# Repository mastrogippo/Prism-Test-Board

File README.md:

# Prism Test Board

[Writeup and pics here]( https://www.mastrogippo.it/2019/09/board-testing-its-fun-they-said/ )

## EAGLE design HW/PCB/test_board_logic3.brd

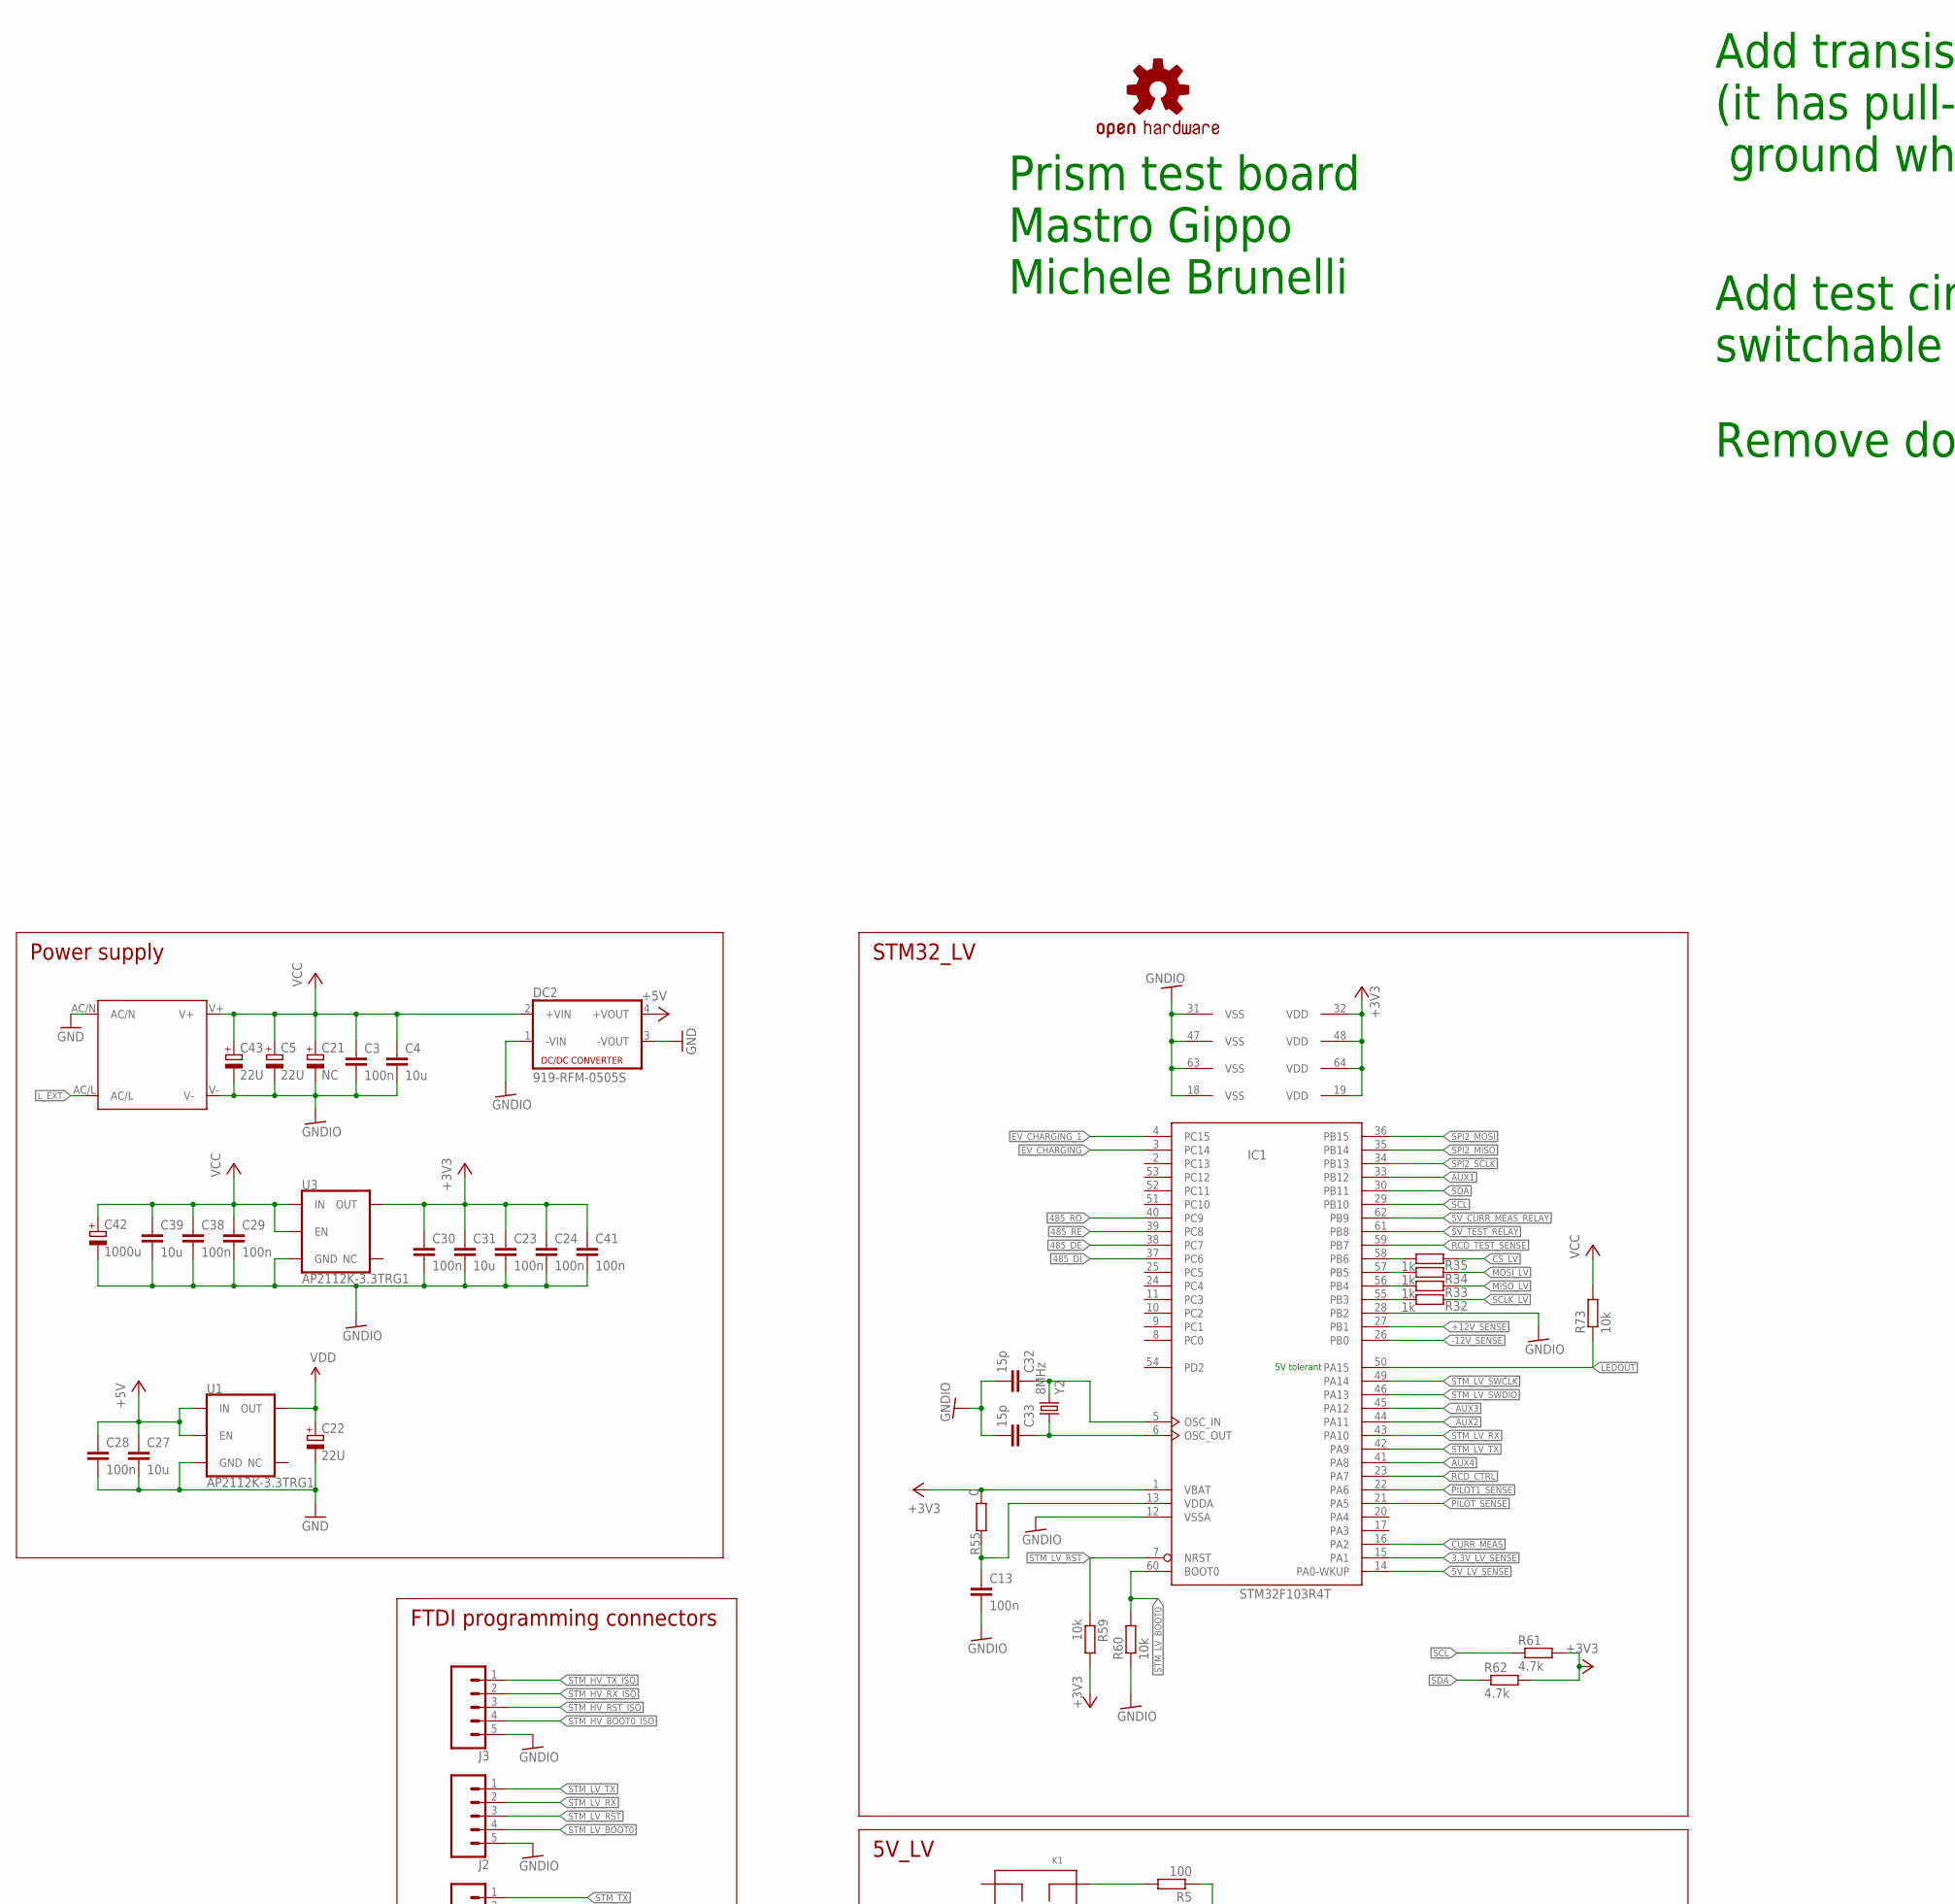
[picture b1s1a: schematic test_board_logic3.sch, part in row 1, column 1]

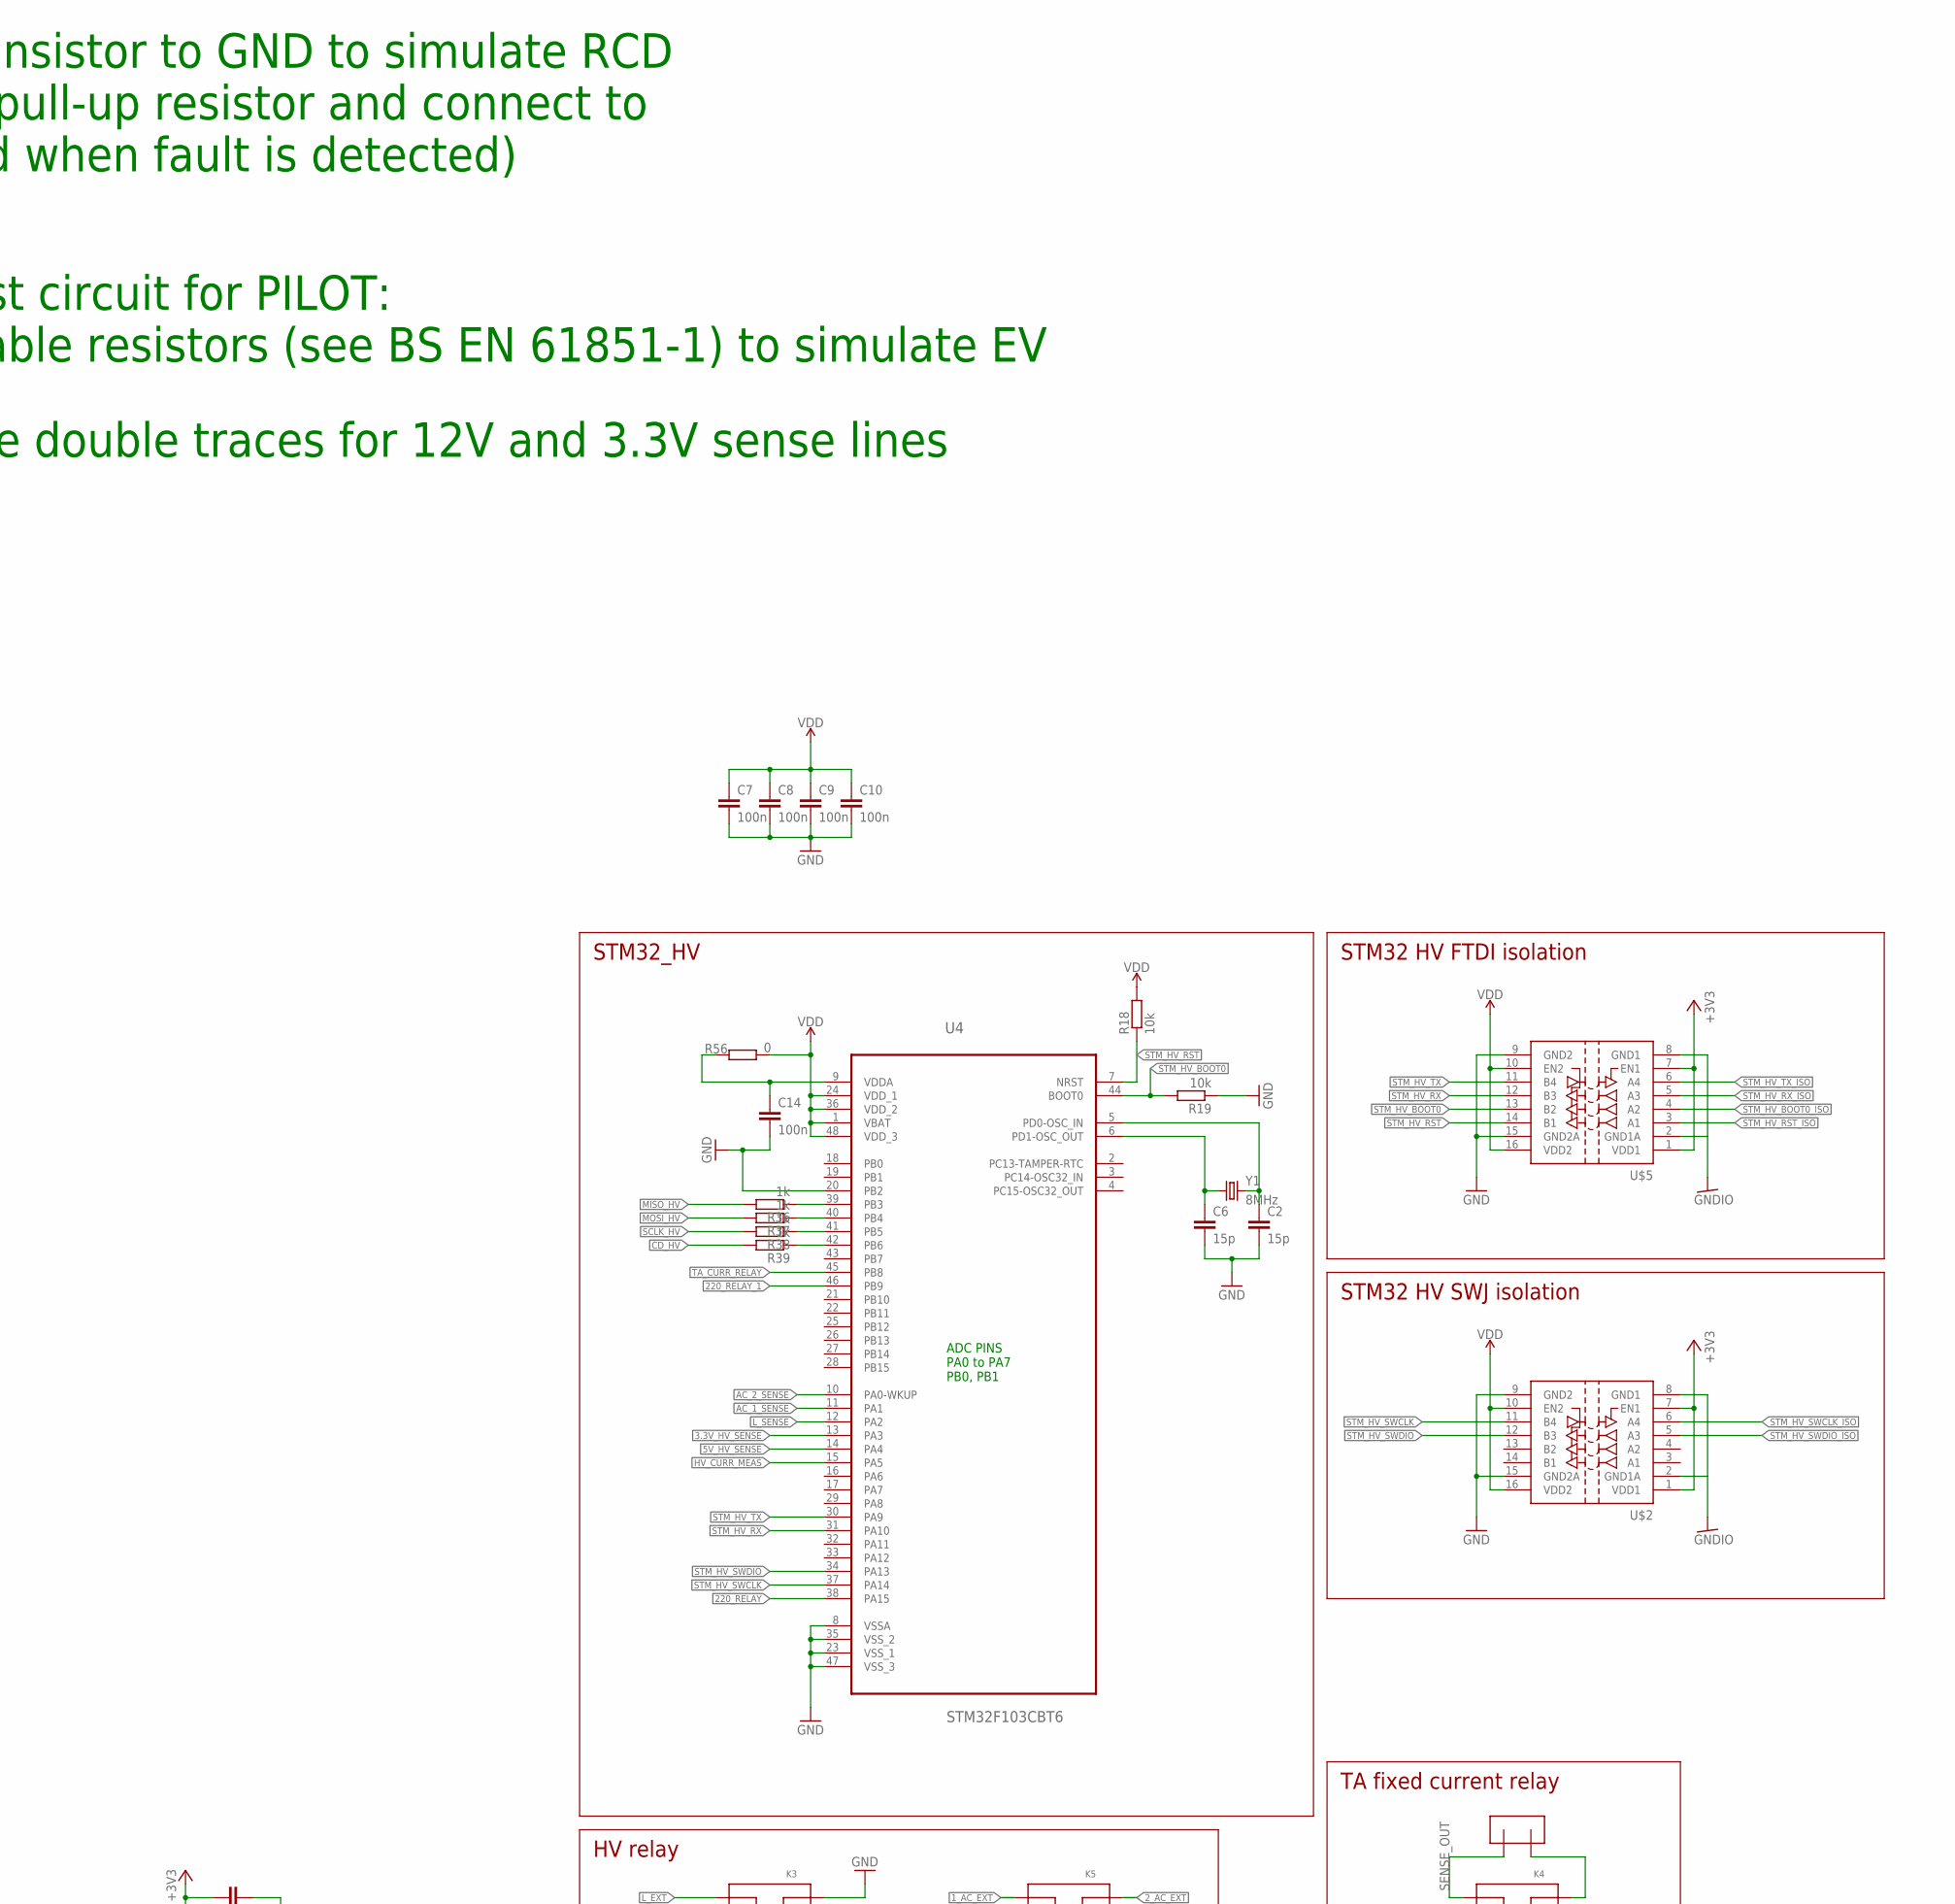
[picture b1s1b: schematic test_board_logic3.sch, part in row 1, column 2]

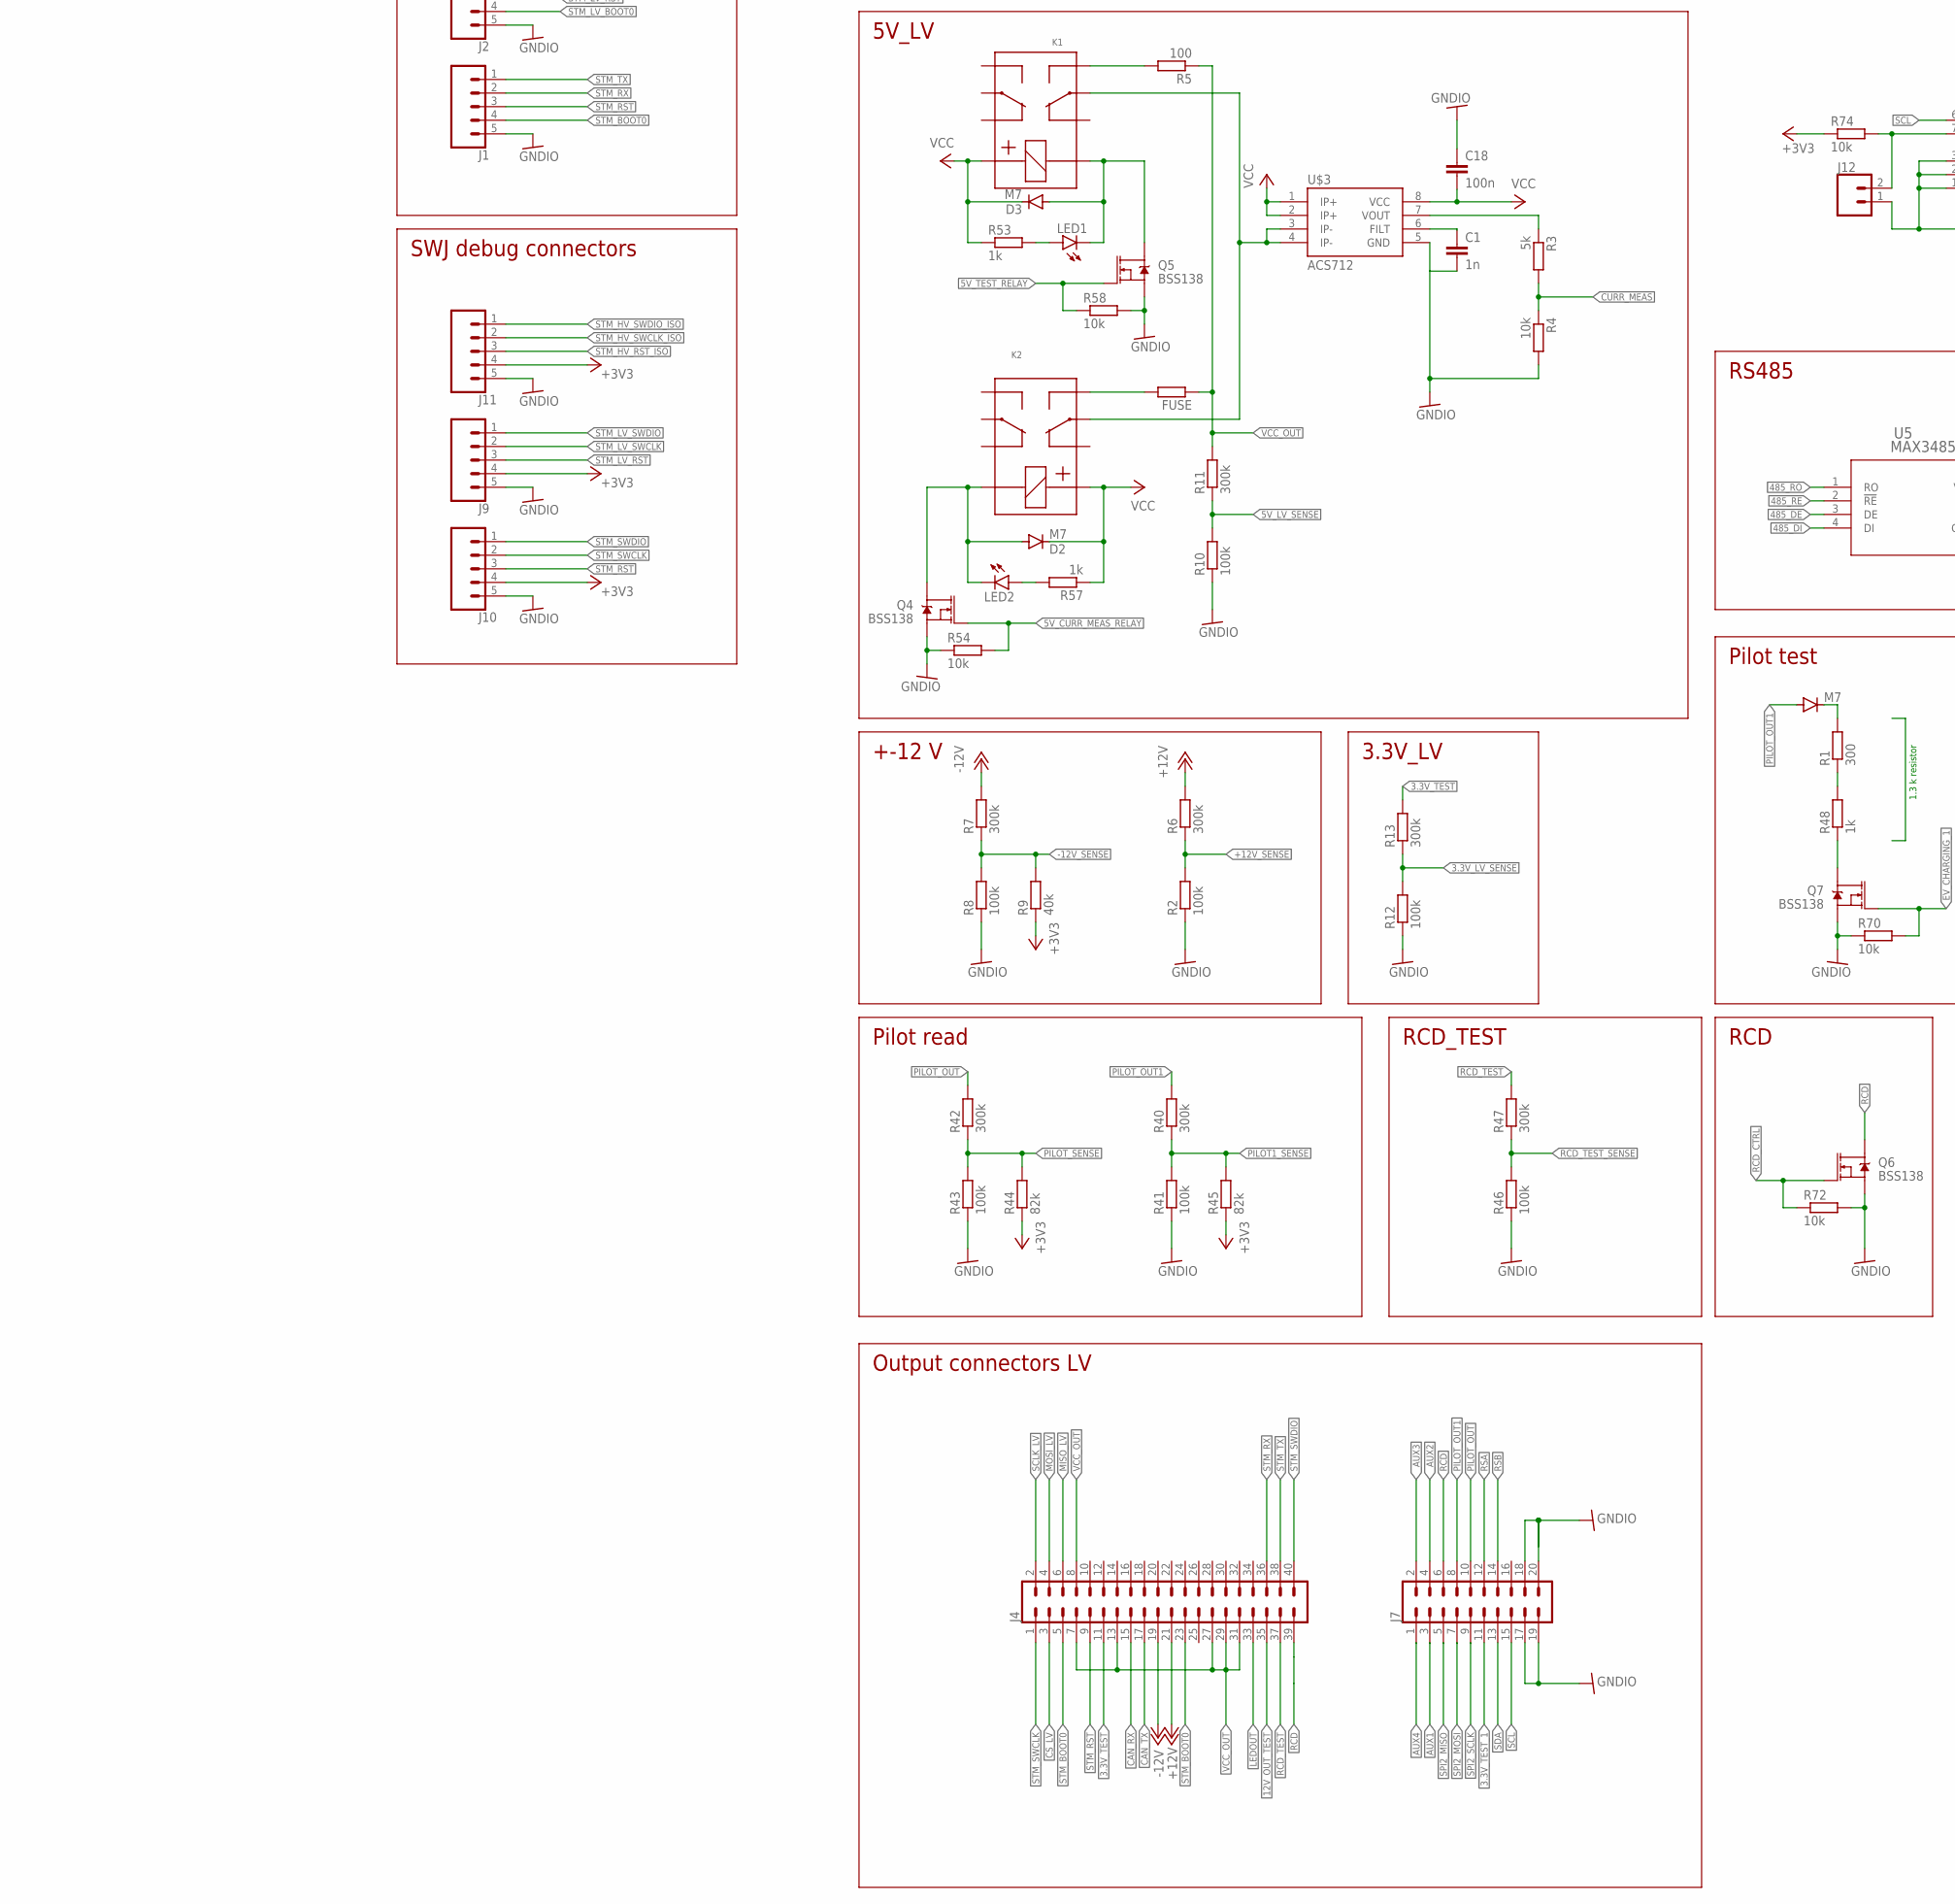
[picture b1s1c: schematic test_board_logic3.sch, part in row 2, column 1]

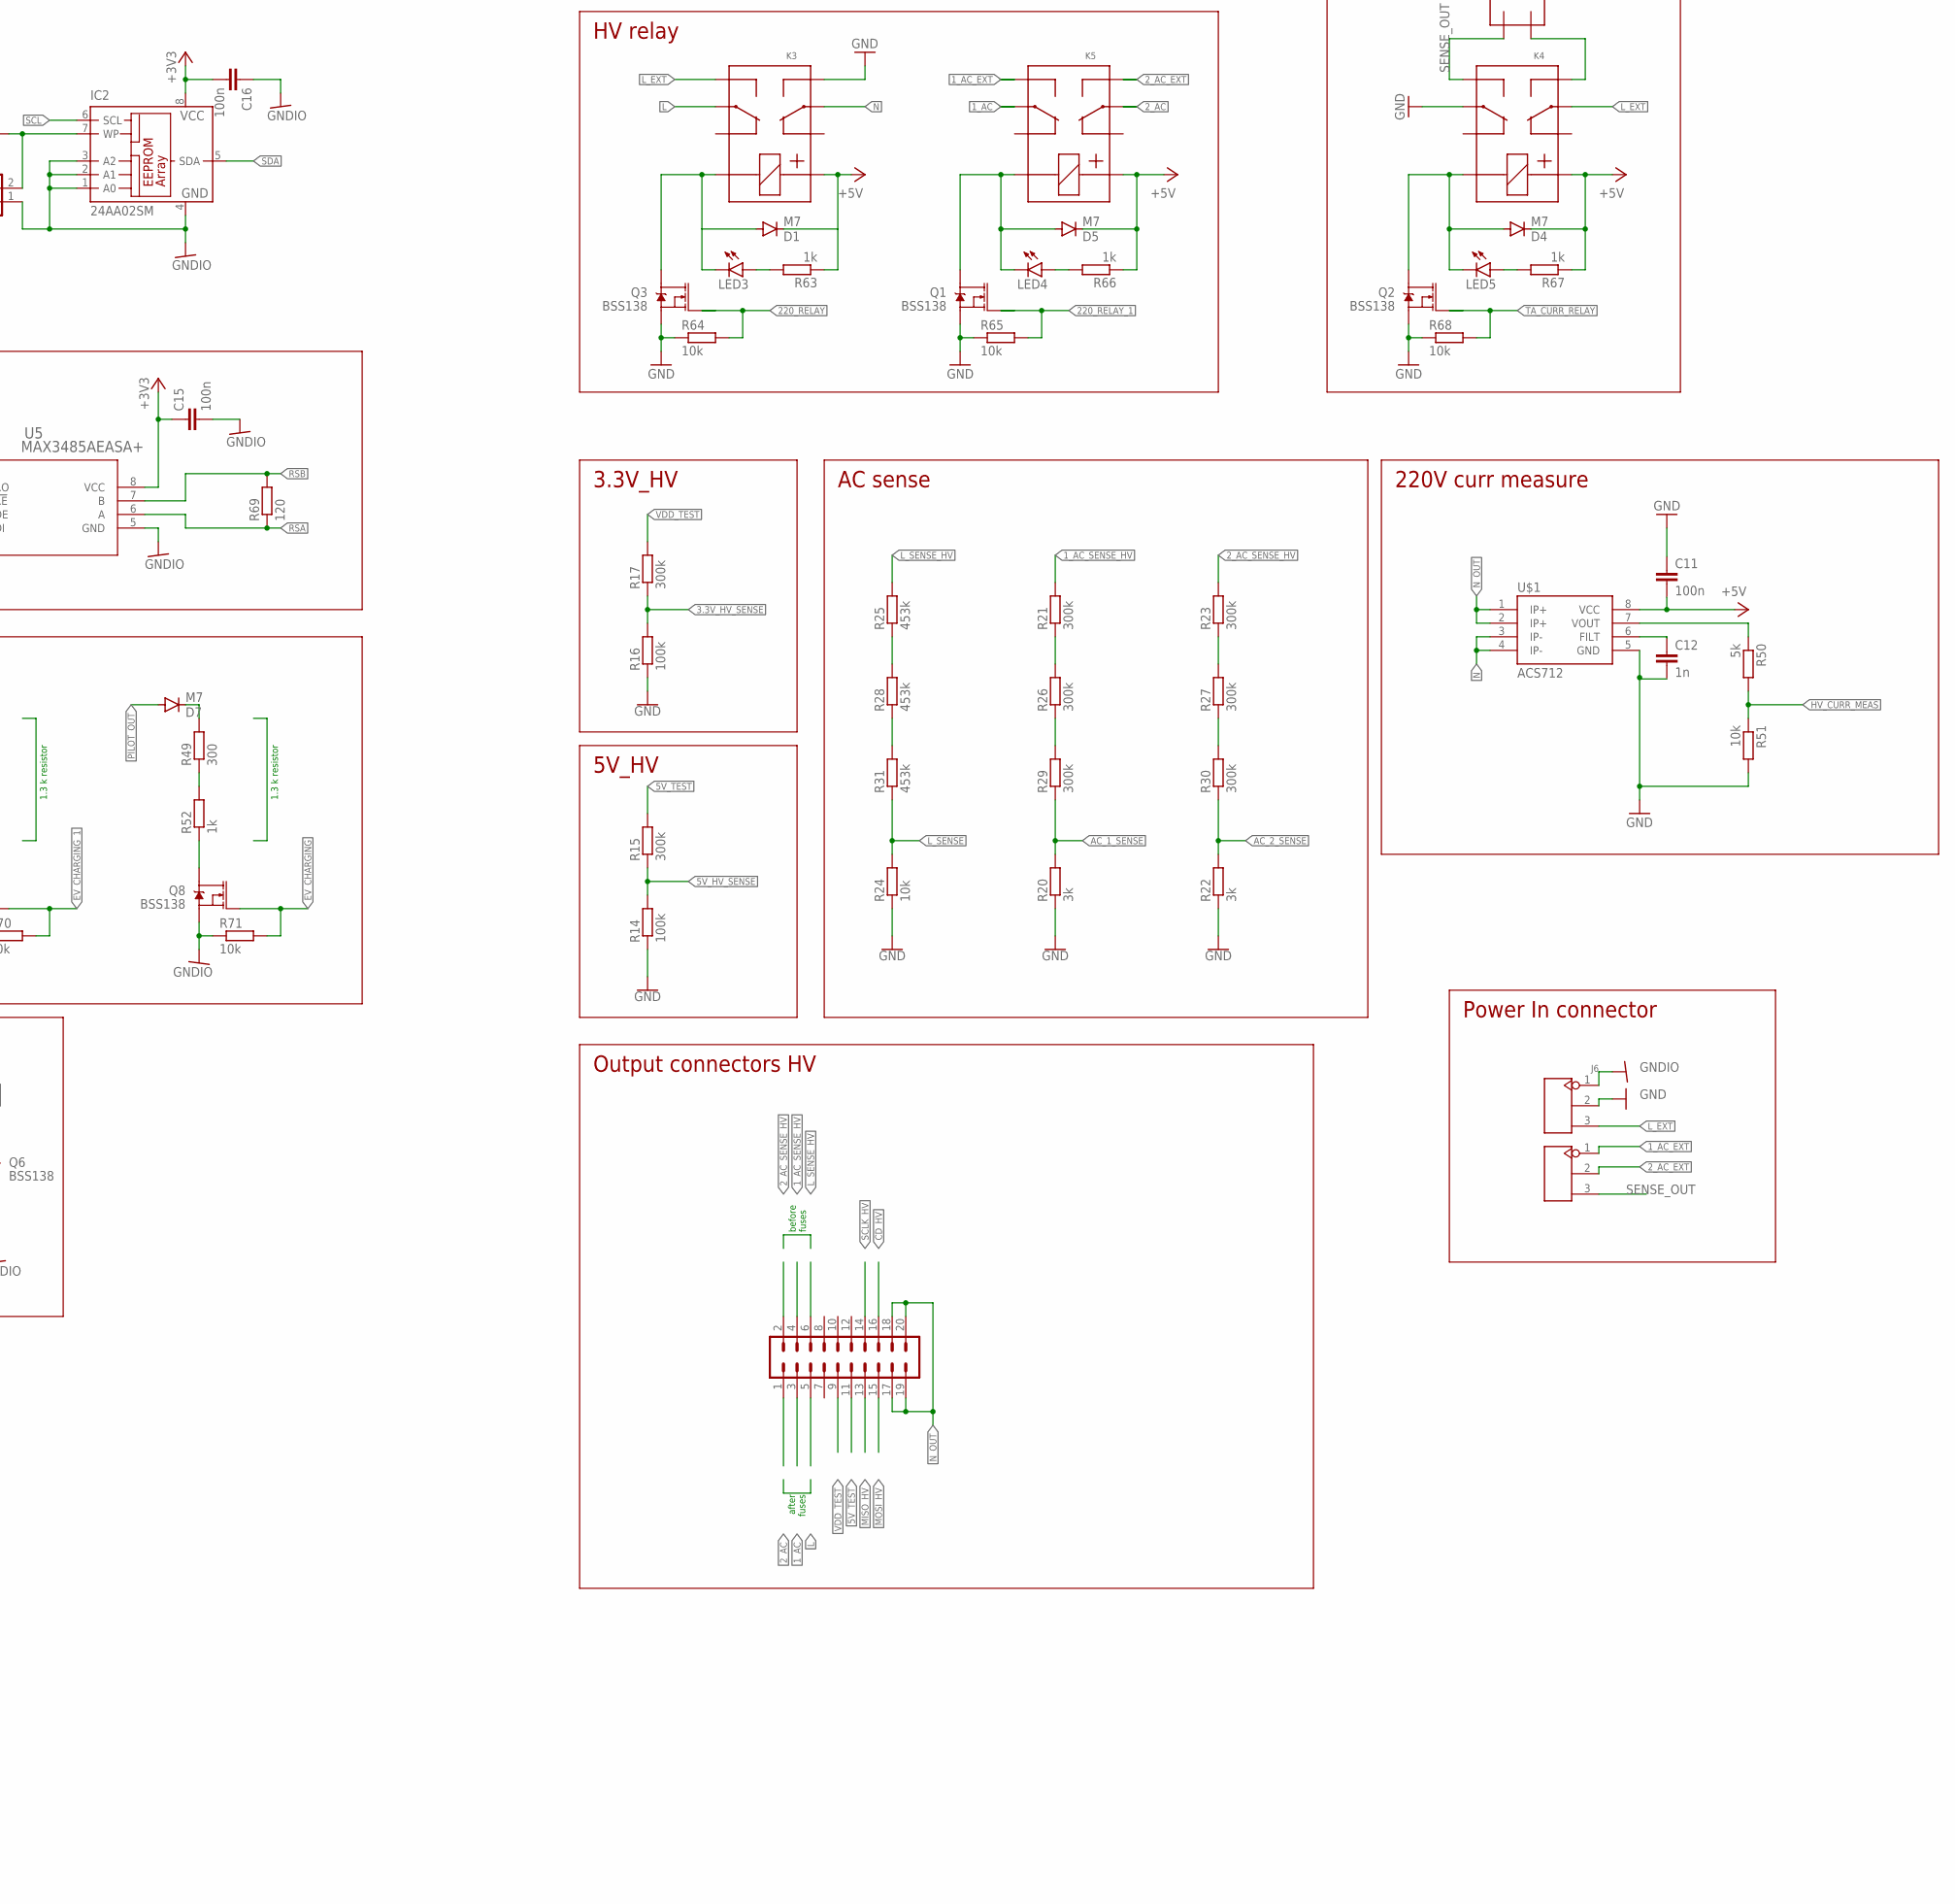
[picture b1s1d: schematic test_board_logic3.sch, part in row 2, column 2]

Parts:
C1, C12: 1n; C0603K
C2, C6, C32, C33: 15p; C0603K
C3, C7, C8, C9, C10, C11, C13, C14, C15, C16, C18, C23, C24, C28, C29, C30, C38, C41: 100n; C0603K
C4, C27, C31, C39: 10u; C0805K
C5, C22, C43: 22U; B/3528-21R
C21: NC; 153CLV-0505
C42: 1000u; E5-10,5
D1, D2, D3, D4, D5, D6, D7: M7; DO-214AC
DC2: 919-RFM-0505S; NME
FUSE: R-EU_R0805; R0805
IC1: STM32F103R4T; LQFP64
IC2: 24AA02SM; SO-08M
J1, J2, J3, J9, J10, J11: 2001R-5P; JST-5-PTH-VERT
J4: CONN_20X2SHROUDED; 2X20_SHROUDED
J5, J6: GREEN-3P-5.0; H3-5.0-15.5X8.0MM
J7, J8: CONN_10X2; 2X10
J12: CONN_02; 1X02
K1, K2, K3, K4, K5: G6S-2
LED1, LED2, LED3, LED4, LED5: LEDSMT1206; 1206
Q1, Q2, Q3, Q4, Q5, Q6, Q7, Q8: BSS138; SOT23-3
R1, R49: 300; R0603
R2, R8, R10, R12, R14, R16, R41, R43, R46: 100k; R0603
R3, R50: 5k; R0603
R4, R18, R19, R24, R51, R54, R58, R59, R60, R64, R65, R68, R70, R71, R72, R73, R74: 10k; R0603
R5: 100; R1210
R6, R7, R11, R13, R15, R17, R21, R23, R26, R27, R29, R30, R40, R42, R47: 300k; R0603
R9: 40k; R0603
R20, R22: 3k; R0603
R25, R28, R31: 453k; R0603
R32, R33, R34, R35, R36, R37, R38, R39, R48, R52, R53, R57, R63, R66, R67: 1k; R0603
R44, R45: 82k; R0603
R55, R56: 0; R0603
R61, R62: 4.7k; R0603
R69: 120; R0603
U1, U3: AP2112K-3.3TRG1; SOT23-5
U4: STM32F103CBT6; QFP50P900X900X160-48N
U5: MAX3485AEASA+; 21-0041B_8
U$1, U$3: ACS712; SO08
U$2, U$5: SI8441IS1; SO16
U$4: NC; IRM_15/20
U$6: 2 PIN STRIP F; STRIP_NOMIDDLE
U$7: OSHW-LOGOL; OSHW-LOGO-L
Y1, Y2: 8MHz; CRYSTAL-SMD-3.2X2.5MM

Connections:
1_AC: J8.3, K5.9
1_AC1: R21.1, R26.2
1_AC2: R26.1, R29.2
1_AC_EXT: J5.1, K5.8
1_AC_SENSE_HV: J8.4, R21.2
2_AC: J8.1, K5.4
2_AC1: R23.1, R27.2
2_AC2: R27.1, R30.2
2_AC_EXT: J5.2, K5.5
2_AC_SENSE_HV: J8.2, R23.2
3.3V_HV_SENSE: R16.2, R17.1, U4.13 (PA3)
3.3V_LV_SENSE: IC1.15 (PA1), R12.2, R13.1
3.3V_TEST: J4.11, R13.2
3.3V_TEST_1: J7.11
5V_CURR_MEAS_RELAY: IC1.62 (PB9), Q4.1 (G), R54.2
5V_HV_SENSE: R14.2, R15.1, U4.14 (PA4)
5V_LV_SENSE: IC1.14 (PA0-WKUP), R10.2, R11.1
5V_TEST: J8.11, R15.2
5V_TEST_RELAY: IC1.61 (PB8), Q5.1 (G), R58.1
12V_OUT_TEST: J4.35
220_RELAY: Q3.1 (G), R64.2, U4.38 (PA15)
220_RELAY_1: Q1.1 (G), R65.2, U4.46 (PB9)
485_DE: IC1.38 (PC7), U5.3 (DE)
485_DI: IC1.37 (PC6), U5.4 (DI)
485_RE: IC1.39 (PC8), U5.2 (!RE)
485_RO: IC1.40 (PC9), U5.1 (RO)
+3V3: C15.1, C16.2, C23.1, C24.1, C30.1, C31.1, C41.1, IC1.1 (VBAT), IC1.19 (VDD), IC1.32 (VDD), IC1.48 (VDD), IC1.64 (VDD), IC2.8 (VCC), J9.4, J10.4, J11.4, R9.1, R44.1, R45.1, R55.1, R59.2, R61.2, R62.2, R74.1, U3.5 (OUT), U5.8 (VCC), U$2.1 (VDD1), U$2.7 (EN1), U$5.1 (VDD1), U$5.7 (EN1)
+5V: C11.2, C27.1, C28.1, D1.C, D4.C, D5.C, DC2.4 (+VOUT), K3.1, K4.1, K5.1, R63.1, R66.1, R67.1, U1.1 (IN), U1.3 (EN), U$1.8 (VCC)
+12V: J4.21, R6.2
+12V_SENSE: IC1.27 (PB1), R2.2, R6.1
-12V: J4.19, R7.2
-12V_SENSE: IC1.26 (PB0), R7.1, R8.2, R9.2
AC_1_SENSE: R20.2, R29.1, U4.11 (PA1)
AC_2_SENSE: R22.2, R30.1, U4.10 (PA0-WKUP)
AUX1: IC1.33 (PB12), J7.3
AUX4: IC1.41 (PA8), J7.1
CAN_RX: J4.15
CAN_TX: J4.17
CD_HV: J8.16, R39.2
CS_LV: J4.3, R35.2
CURR_MEAS: IC1.16 (PA2), R3.2, R4.1
EV_CHARGING: IC1.3 (PC14), Q8.1 (G), R71.2
EV_CHARGING_1: IC1.4 (PC15), Q7.1 (G), R70.2
GND: C2.2, C6.2, C7.2, C8.2, C9.2, C10.2, C11.1, C12.2, C14.2, C22.-, C27.2, C28.2, DC2.3 (-VOUT), J6.2, K3.5, K4.9, Q1.2 (S), Q2.2 (S), Q3.2 (S), R14.1, R16.1, R19.1, R20.1, R22.1, R24.1, R51.2, R64.1, R65.1, R68.1, U1.2 (GND), U4.8 (VSSA), U4.20 (PB2), U4.23 (VSS_1), U4.35 (VSS_2), U4.47 (VSS_3), U$1.5 (GND), U$2.9 (GND2), U$2.15 (GND2A), U$4.AC/N, U$5.9 (GND2), U$5.15 (GND2A)
GNDIO: C1.2, C3.2, C4.2, C5.-, C13.2, C15.2, C16.1, C18.1, C21.-, C23.2, C24.2, C29.2, C30.2, C31.2, C32.2, C33.2, C38.2, C39.2, C41.2, C42.-, C43.-, DC2.1 (-VIN), IC1.12 (VSSA), IC1.18 (VSS), IC1.28 (PB2), IC1.31 (VSS), IC1.47 (VSS), IC1.63 (VSS), IC2.1 (A0), IC2.2 (A1), IC2.3 (A2), IC2.4 (GND), J1.5, J2.5, J3.5, J6.1, J7.17, J7.18, J7.19, J7.20, J9.5, J10.5, J11.5, J12.1, Q4.2 (S), Q5.2 (S), Q6.2 (S), Q7.2 (S), Q8.2 (S), R2.1, R4.2, R8.1, R10.1, R12.1, R41.1, R43.1, R46.1, R54.1, R58.2, R60.1, R70.1, R71.1, R72.2, U3.2 (GND), U5.5 (GND), U$2.2 (GND1A), U$2.8 (GND1), U$3.5 (GND), U$4.V-, U$5.2 (GND1A), U$5.8 (GND1)
HV_CURR_MEAS: R50.2, R51.1, U4.15 (PA5)
L: J8.5, K3.9
L1: R25.1, R28.2
L2: R28.1, R31.2
LEDOUT: IC1.50 (PA15), J4.33, R73.1
L_EXT: J6.3, K3.8, K4.4, U$4.AC/L
L_SENSE: R24.2, R31.1, U4.12 (PA2)
L_SENSE_HV: J8.6, R25.2
MISO_HV: J8.13, R36.2
MISO_LV: J4.6, R33.2
MOSI_HV: J8.15, R37.2
MOSI_LV: J4.4, R34.2
N: K3.4, U$1.3 (IP-), U$1.4 (IP-)
unnamed: R3.1, U$3.7 (VOUT)
unnamed: FUSE.2, K2.5
unnamed: IC2.7 (WP), J12.2, R74.2
unnamed: C2.1, U4.5 (PD0-OSC_IN), Y1.3 (2)
unnamed: C1.1, U$3.6 (FILT)
unnamed: IC1.55 (PB3), R32.1
unnamed: C6.1, U4.6 (PD1-OSC_OUT), Y1.1
unnamed: K1.8, R5.2
unnamed: IC1.56 (PB4), R33.1
unnamed: K1.9, K2.4, U$3.3 (IP-), U$3.4 (IP-)
unnamed: C33.1, IC1.6 (OSC_OUT), Y2.1
unnamed: IC1.57 (PB5), R34.1
unnamed: IC1.58 (PB6), R35.1
unnamed: R36.1, U4.39 (PB3)
unnamed: R37.1, U4.40 (PB4)
unnamed: R38.1, U4.41 (PB5)
unnamed: R39.1, U4.42 (PB6)
unnamed: C12.1, U$1.6 (FILT)
unnamed: D4.A, K4.12, LED5.C, Q2.3 (D)
unnamed: R50.1, U$1.7 (VOUT)
unnamed: K4.5, U$6.P$1
unnamed: D1.A, K3.12, LED3.C, Q3.3 (D)
unnamed: D5.A, K5.12, LED4.C, Q1.3 (D)
unnamed: D2.A, K2.12, LED2.C, Q4.3 (D)
unnamed: D3.A, K1.12, LED1.C, Q5.3 (D)
unnamed: C13.1, IC1.13 (VDDA), R55.2
unnamed: C14.1, R56.2, U4.9 (VDDA)
unnamed: D6.C, R1.2
unnamed: Q7.3 (D), R48.1
unnamed: R49.1, R52.2
unnamed: Q8.3 (D), R52.1
unnamed: R1.1, R48.2
unnamed: LED1.A, R53.2
unnamed: LED5.A, R67.2
unnamed: LED2.A, R57.2
unnamed: LED3.A, R63.2
unnamed: LED4.A, R66.2
unnamed: D7.C, R49.2
unnamed: C32.1, IC1.5 (OSC_IN), Y2.3 (2)
N_OUT: J8.17, J8.18, J8.19, J8.20, U$1.1 (IP+), U$1.2 (IP+)
PA11: U4.32 (PA11)
PILOT1_SENSE: IC1.22 (PA6), R40.1, R41.2, R45.2
PILOT_OUT: D7.A, J7.10, R42.2
PILOT_OUT1: D6.A, J7.8, R40.2
PILOT_SENSE: IC1.21 (PA5), R42.1, R43.2, R44.2
RCD: J4.39, J7.6, Q6.3 (D)
RCD_CTRL: IC1.23 (PA7), Q6.1 (G), R72.1
RCD_TEST: J4.37, R47.2
RCD_TEST_SENSE: IC1.59 (PB7), R46.2, R47.1
RSA: J7.12, R69.1, U5.6 (A)
RSB: J7.14, R69.2, U5.7 (B)
SCL: IC1.29 (PB10), IC2.6 (SCL), J7.15, R61.1
SCLK_HV: J8.14, R38.2
SCLK_LV: J4.2, R32.2
SDA: IC1.30 (PB11), IC2.5 (SDA), J7.13, R62.1
SENSE_OUT: J5.3, K4.8, U$6.P$2
SPI2_MISO: IC1.35 (PB14), J7.5
SPI2_MOSI: IC1.36 (PB15), J7.7
SPI2_SCLK: IC1.34 (PB13), J7.9
STM_BOOT0: J1.4, J4.5, J4.23
STM_HV_BOOT0: R19.2, U4.44 (BOOT0), U$5.13 (B2)
STM_HV_BOOT0_ISO: J3.4, U$5.4 (A2)
STM_HV_RST: R18.1, U4.7 (NRST), U$5.14 (B1)
STM_HV_RST_ISO: J3.3, J11.3, U$5.3 (A1)
STM_HV_RX: U4.31 (PA10), U$5.12 (B3)
STM_HV_RX_ISO: J3.2, U$5.5 (A3)
STM_HV_SWCLK: U4.37 (PA14), U$2.11 (B4)
STM_HV_SWCLK_ISO: J11.2, U$2.6 (A4)
STM_HV_SWDIO: U4.34 (PA13), U$2.12 (B3)
STM_HV_SWDIO_ISO: J11.1, U$2.5 (A3)
STM_HV_TX: U4.30 (PA9), U$5.11 (B4)
STM_HV_TX_ISO: J3.1, U$5.6 (A4)
STM_LV_BOOT0: IC1.60 (BOOT0), J2.4, R60.2
STM_LV_RST: IC1.7 (NRST), J2.3, J9.3, R59.1
STM_LV_RX: IC1.43 (PA10), J2.2
STM_LV_SWCLK: IC1.49 (PA14), J9.2
STM_LV_SWDIO: IC1.46 (PA13), J9.1
STM_LV_TX: IC1.42 (PA9), J2.1
STM_RST: J1.3, J4.9, J10.3
STM_RX: J1.2, J4.36
STM_SWCLK: J4.1, J10.2
STM_SWDIO: J4.40, J10.1
STM_TX: J1.1, J4.38
TA_CURR_RELAY: Q2.1 (G), R68.2, U4.45 (PB8)
VCC: C3.1, C4.1, C5.+, C18.2, C21.+, C29.1, C38.1, C39.1, C42.+, C43.+, D2.C, D3.C, DC2.2 (+VIN), K1.1, K2.1, R53.1, R57.1, R73.2, U3.1 (IN), U3.3 (EN), U$3.1 (IP+), U$3.2 (IP+), U$3.8 (VCC), U$4.V+
VCC_OUT: FUSE.1, J4.7, J4.8, J4.13, J4.27, J4.29, J4.31, R5.1, R11.2
VDD: C7.1, C8.1, C9.1, C10.1, C22.+, R18.2, R56.1, U1.5 (OUT), U4.1 (VBAT), U4.24 (VDD_1), U4.36 (VDD_2), U4.48 (VDD_3), U$2.10 (EN2), U$2.16 (VDD2), U$5.10 (EN2), U$5.16 (VDD2)
VDD_TEST: J8.9, R17.2
_AUX2: IC1.44 (PA11), J7.4
_AUX3: IC1.45 (PA12), J7.2

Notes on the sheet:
+-12 V
5V_LV
Power supply
3.3V_LV
5V_HV
3.3V_HV
STM32_LV
STM32_HV
AC sense
HV relay
Pilot read
Output connectors LV
Output connectors HV
before fuses
after fuses
RCD_TEST
FTDI programming connectors
STM32 HV FTDI isolation
220V curr measure
TA fixed current relay
STM32 HV SWJ isolation
SWJ debug connectors
Power In connector
ADC PINS PA0 to PA7 PB0, PB1
Add transistor to GND to simulate RCD (it has pull-up resistor and connect to ground when fault is detected)
Add test circuit for PILOT: switchable resistors (see BS EN 61851-1) to simulate EV
Remove double traces for 12V and 3.3V sense lines
RCD
1.3 k resistor
Pilot test
RS485
5V tolerant
Prism test board Mastro Gippo Michele Brunelli

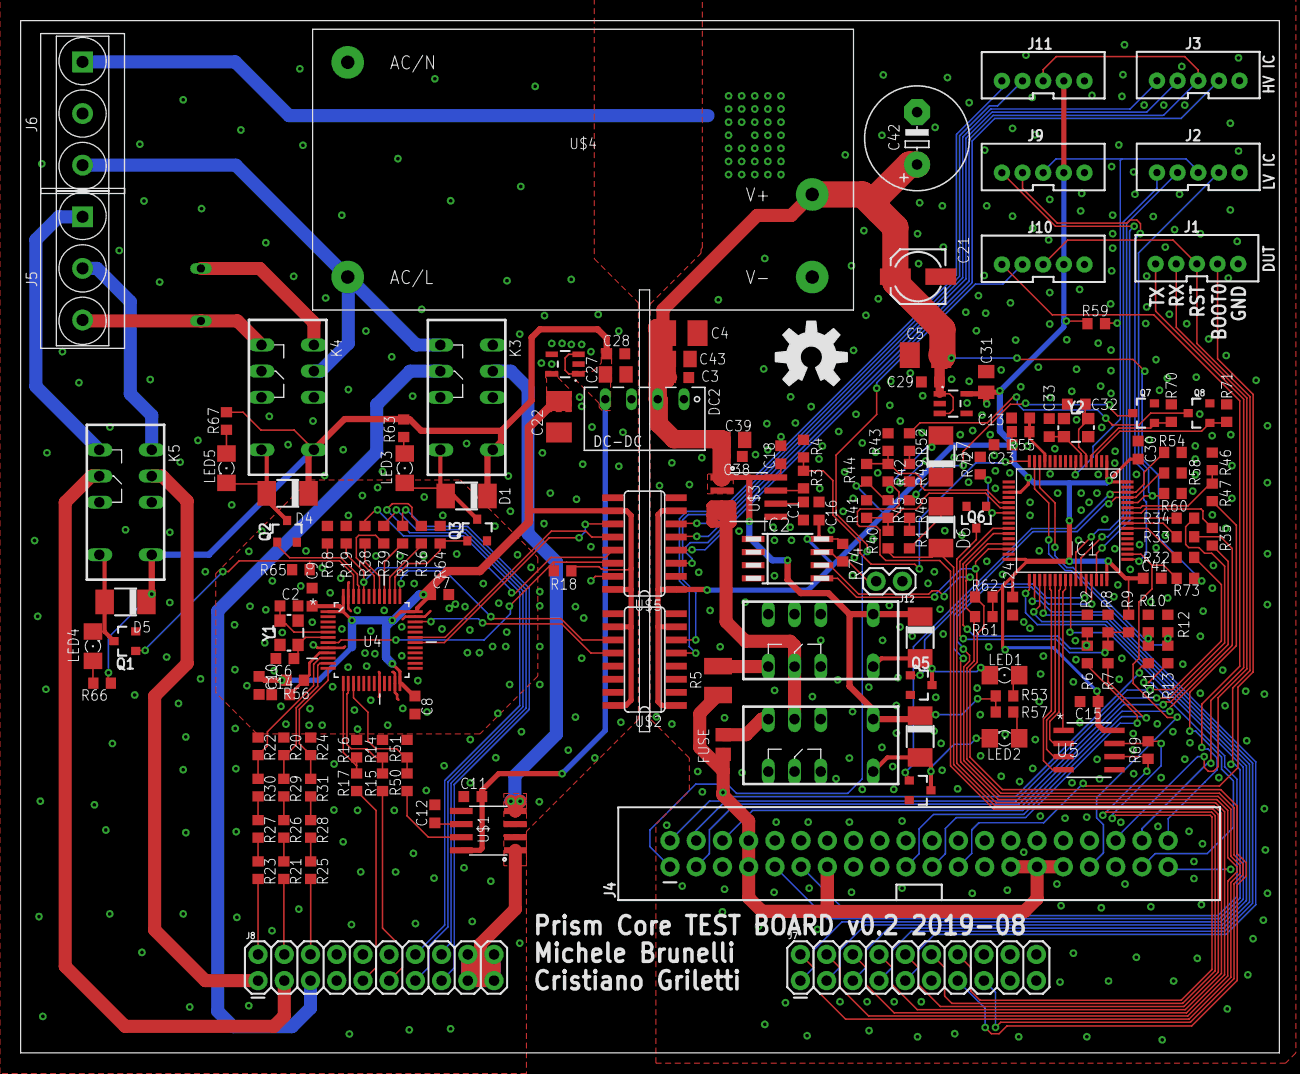
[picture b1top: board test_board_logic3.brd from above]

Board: 2 copper layers, 121.9 x 100.0 mm, 161 parts (0 on the bottom side), 143 nets.

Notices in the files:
parts and their libraries:
SparkFun-Connectors: Licensing: Creative Commons ShareAlike 4.0 International - https://creativecommons.org/licenses/by-sa/4.0
